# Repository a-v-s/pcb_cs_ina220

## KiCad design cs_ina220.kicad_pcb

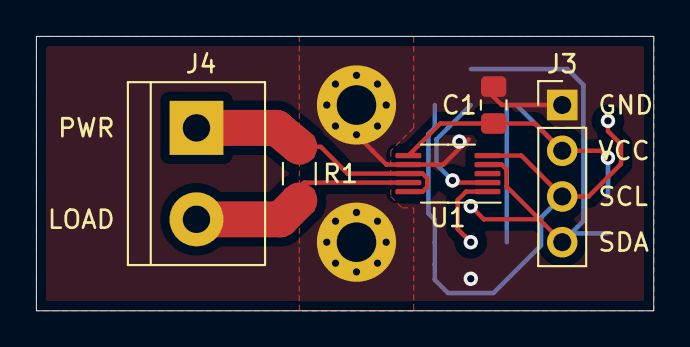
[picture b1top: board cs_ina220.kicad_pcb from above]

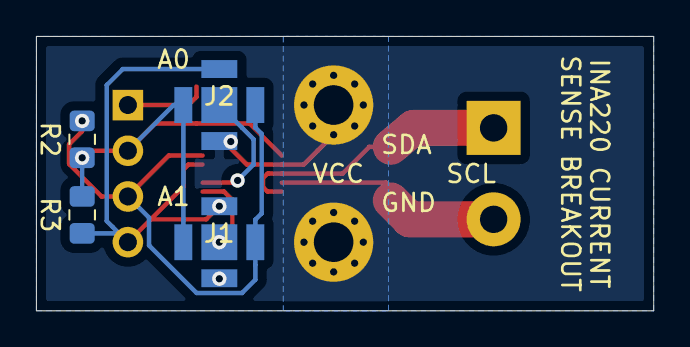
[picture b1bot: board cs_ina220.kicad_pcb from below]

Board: 2 copper layers, 34.3 x 15.2 mm, 11 parts (4 on the bottom side), 8 nets.

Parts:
C1: C_Small; C_0805_2012Metric_Pad1.15x1.40mm_HandSolder
H1, H2: MountingHole_Pad; MountingHole_2.2mm_M2_Pad_Via
J1, J2: Conn_01x05; SolderJumper-5
J3: Conn_01x04; PinHeader_1x04_P2.54mm_Vertical
J4: Conn_01x02; TerminalBlock_bornier-2_P5.08mm
R1: R_Small; R_1206_3216Metric_Pad1.42x1.75mm_HandSolder
R2, R3: R_Small; R_0805_2012Metric_Pad1.15x1.40mm_HandSolder
U1: INA220; VSSOP-10_3x3mm_P0.5mm

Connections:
A0: J2.1, U1.2
A1: J1.1, U1.1
GND: C1.1, H1.1, H2.1, J1.2, J2.2, J3.1, U1.7
LOAD: J4.2, R1.2, U1.9
SCL: J1.5, J2.5, J3.3, R2.2, U1.5
SDA: J1.4, J2.4, J3.4, R3.2, U1.4
SUPPLY: J4.1, R1.1, U1.8, U1.10
VCC: C1.2, J1.3, J2.3, J3.2, R2.1, R3.1, U1.6

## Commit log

2020-01-04 INA220 Breakout v1.0
